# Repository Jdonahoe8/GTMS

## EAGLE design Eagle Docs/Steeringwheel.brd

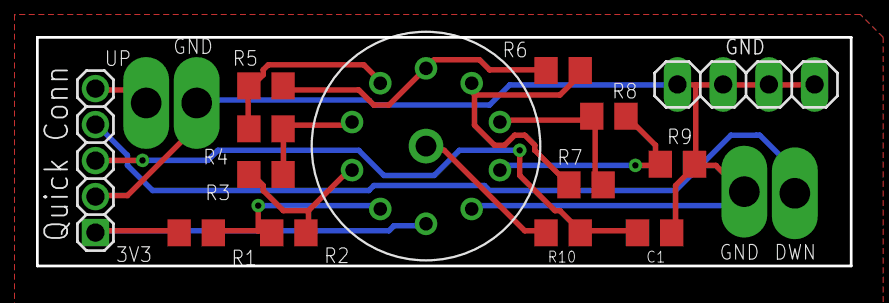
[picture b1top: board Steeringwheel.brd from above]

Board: 2 copper layers, 45.2 x 12.7 mm, 18 parts (0 on the bottom side), 14 nets.

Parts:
C1: C0805
GND: PINHD-1X4; 1X04
QUICK_CONN: PINHD-1X55X2MM; 1_05X2MM
R1, R2, R3, R4, R5, R6, R7, R8, R9, R10: R0805
SHIFT-DOWN_GND: PTR1PAD1-17Y; P1-17Y
SHIFT-DOWN_SIGNAL: PTR1PAD1-17Y; P1-17Y
SHIFT-UP_GND: PTR1PAD1-17Y; P1-17Y
SHIFT-UP_SIGNAL: PTR1PAD1-17Y; P1-17Y
U$1: 56DP36-01-1-AJN

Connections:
+5V: QUICK_CONN.1, R1.1, U$1.P1
GND: C1.1, GND.1, GND.2, GND.3, GND.4, QUICK_CONN.2, R9.2, SHIFT-DOWN_GND.TP, SHIFT-UP_GND.TP, U$1.P10
unnamed: R1.2, R2.1, U$1.P2
unnamed: R2.2, R3.1, U$1.P3
unnamed: R3.2, R4.1, U$1.P4
unnamed: R5.2, R6.1, U$1.P6
unnamed: R6.2, R7.1, U$1.P7
unnamed: R7.2, R8.1, U$1.P8
unnamed: R8.2, R9.1, U$1.P9
unnamed: QUICK_CONN.5, SHIFT-UP_SIGNAL.TP
unnamed: QUICK_CONN.4, SHIFT-DOWN_SIGNAL.TP
unnamed: R4.2, R5.1, U$1.P5
unnamed: R10.2, U$1.COMMON
OUTPUT: C1.2, QUICK_CONN.3, R10.1

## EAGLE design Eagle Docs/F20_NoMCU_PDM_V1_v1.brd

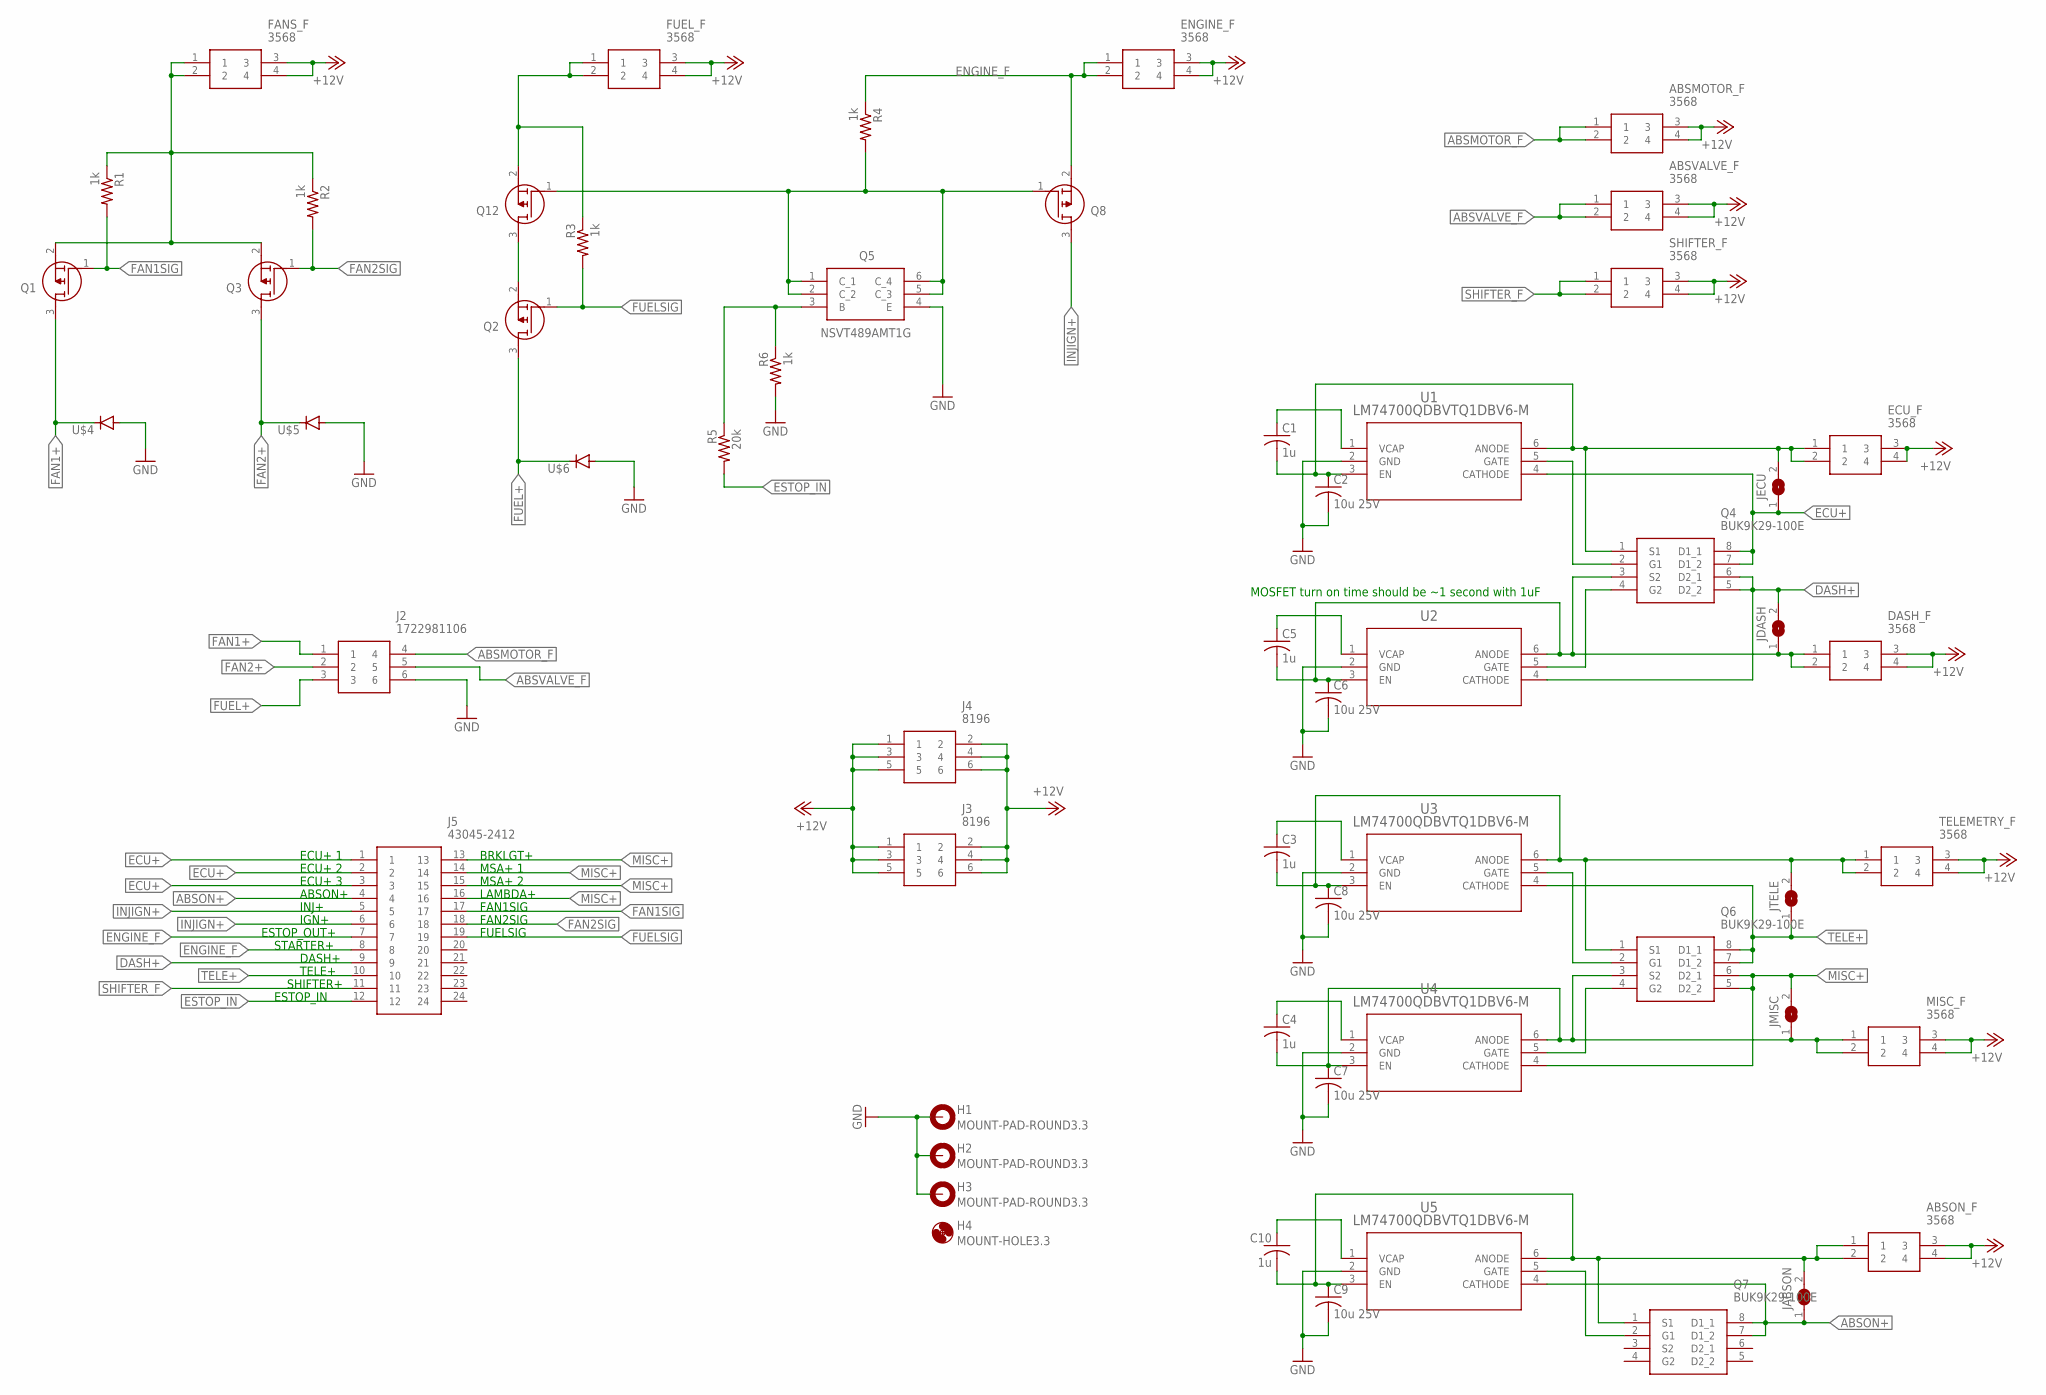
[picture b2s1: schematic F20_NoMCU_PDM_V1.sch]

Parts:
ABSMOTOR_F: 3568
ABSON_F: 3568
ABSVALVE_F: 3568
C1, C3, C4, C5, C10: 1u; C0805
C2, C6, C7, C8, C9: 10u 25V; C0805
DASH_F: 3568
ECU_F: 3568
ENGINE_F: 3568
FANS_F: 3568
FUEL_F: 3568
H1, H2, H3: MOUNT-PAD-ROUND3.3; 3,3-PAD
H4: MOUNT-HOLE3.3; 3,3
J2: 1722981106
J3, J4: 8196
J5: 43045-2412
JABSON: SJ
JDASH: SJ
JECU: SJ
JMISC: SJ
JTELE: SJ
MISC_F: 3568
Q1, Q2, Q3, Q8, Q12: IPB120P04P4L03ATMA1; PG-TO263-3-2_1
Q4, Q6, Q7: BUK9K29-100E; SOIC127P605X105-8N
Q5: NSVT489AMT1G; SOT95P275X110-6N
R1, R2, R3, R4, R6: 1k; R0805
R5: 20k; R0805
SHIFTER_F: 3568
TELEMETRY_F: 3568
U1, U2, U3, U4, U5: LM74700QDBVTQ1DBV6-M; DBV6-M
U$4, U$5, U$6: S10AL-TP; DIOM7959X265N

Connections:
+12V: ABSMOTOR_F.3, ABSMOTOR_F.4, ABSON_F.3, ABSON_F.4, ABSVALVE_F.3, ABSVALVE_F.4, DASH_F.3, DASH_F.4, ECU_F.3, ECU_F.4, ENGINE_F.3, ENGINE_F.4, FANS_F.3, FANS_F.4, FUEL_F.3, FUEL_F.4, J3.1, J3.2, J3.3, J3.4, J3.5, J3.6, J4.1, J4.2, J4.3, J4.4, J4.5, J4.6, MISC_F.3, MISC_F.4, SHIFTER_F.3, SHIFTER_F.4, TELEMETRY_F.3, TELEMETRY_F.4
ABSMOTOR_F: ABSMOTOR_F.1, ABSMOTOR_F.2, J2.4
ABSON+: J5.4, JABSON.1, Q7.7 (D1_2), Q7.8 (D1_1), U5.4 (CATHODE)
ABSVALVE_F: ABSVALVE_F.1, ABSVALVE_F.2, J2.5
DASH+: J5.9, JDASH.2, Q4.5 (D2_2), Q4.6 (D2_1), U2.4 (CATHODE)
ECU+: J5.1, J5.2, J5.3, JECU.1, Q4.7 (D1_2), Q4.8 (D1_1), U1.4 (CATHODE)
ENGINE_F: ENGINE_F.1, ENGINE_F.2, J5.7, J5.8, Q8.2 (S), R4.1
ESTOP_IN: J5.12, R5.2
FAN1+: J2.1, Q1.3 (D), U$4.C
FAN1SIG: J5.17, Q1.1 (G), R1.2
FAN2+: J2.2, Q3.3 (D), U$5.C
FAN2SIG: J5.18, Q3.1 (G), R2.2
FUEL+: J2.3, Q2.3 (D), U$6.C
FUELSIG: J5.19, Q2.1 (G), R3.2
GND: C2.2, C6.2, C7.2, C8.2, C9.2, H1.B3,3, H2.B3,3, H3.B3,3, J2.6, Q5.4 (E), R6.2, U1.2 (GND), U2.2 (GND), U3.2 (GND), U4.2 (GND), U5.2 (GND), U$4.A, U$5.A, U$6.A
INJIGN+: J5.5, J5.6, Q8.3 (D)
MISC+: J5.13, J5.14, J5.15, J5.16, JMISC.2, Q6.5 (D2_2), Q6.6 (D2_1), U4.4 (CATHODE)
unnamed: FANS_F.1, FANS_F.2, Q1.2 (S), Q3.2 (S), R1.1, R2.1
unnamed: FUEL_F.1, FUEL_F.2, Q12.2 (S), R3.1
unnamed: Q2.2 (S), Q12.3 (D)
unnamed: C1.2, C2.1, ECU_F.1, ECU_F.2, JECU.2, Q4.1 (S1), U1.3 (EN), U1.6 (ANODE)
unnamed: Q5.3 (B), R5.1, R6.1
unnamed: C1.1, U1.1 (VCAP)
unnamed: Q5.1 (C_1), Q5.2 (C_2), Q5.5 (C_3), Q5.6 (C_4), Q8.1 (G), Q12.1 (G), R4.2
unnamed: C5.1, U2.1 (VCAP)
unnamed: C5.2, C6.1, DASH_F.1, DASH_F.2, JDASH.1, Q4.3 (S2), U2.3 (EN), U2.6 (ANODE)
unnamed: ABSON_F.1, ABSON_F.2, C9.1, C10.2, JABSON.2, Q7.1 (S1), U5.3 (EN), U5.6 (ANODE)
unnamed: Q4.2 (G1), U1.5 (GATE)
unnamed: C10.1, U5.1 (VCAP)
unnamed: Q4.4 (G2), U2.5 (GATE)
unnamed: C3.1, U3.1 (VCAP)
unnamed: C4.1, U4.1 (VCAP)
unnamed: Q7.2 (G1), U5.5 (GATE)
unnamed: C4.2, C7.1, JMISC.1, MISC_F.1, MISC_F.2, Q6.3 (S2), U4.3 (EN), U4.6 (ANODE)
unnamed: C3.2, C8.1, JTELE.2, Q6.1 (S1), TELEMETRY_F.1, TELEMETRY_F.2, U3.3 (EN), U3.6 (ANODE)
unnamed: Q6.2 (G1), U3.5 (GATE)
unnamed: Q6.4 (G2), U4.5 (GATE)
SHIFTER_F: J5.11, SHIFTER_F.1, SHIFTER_F.2
TELE+: J5.10, JTELE.1, Q6.7 (D1_2), Q6.8 (D1_1), U3.4 (CATHODE)

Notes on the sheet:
ECU+ 1
ECU+ 2
ECU+ 3
ABSON+
INJ+
IGN+
ESTOP_OUT+
STARTER+
DASH+
TELE+
SHIFTER+
BRKLGT+
MSA+ 1
MSA+ 2
LAMBDA+
ESTOP_IN
MOSFET turn on time should be ~1 second with 1uF
FAN1SIG
FAN2SIG
FUELSIG

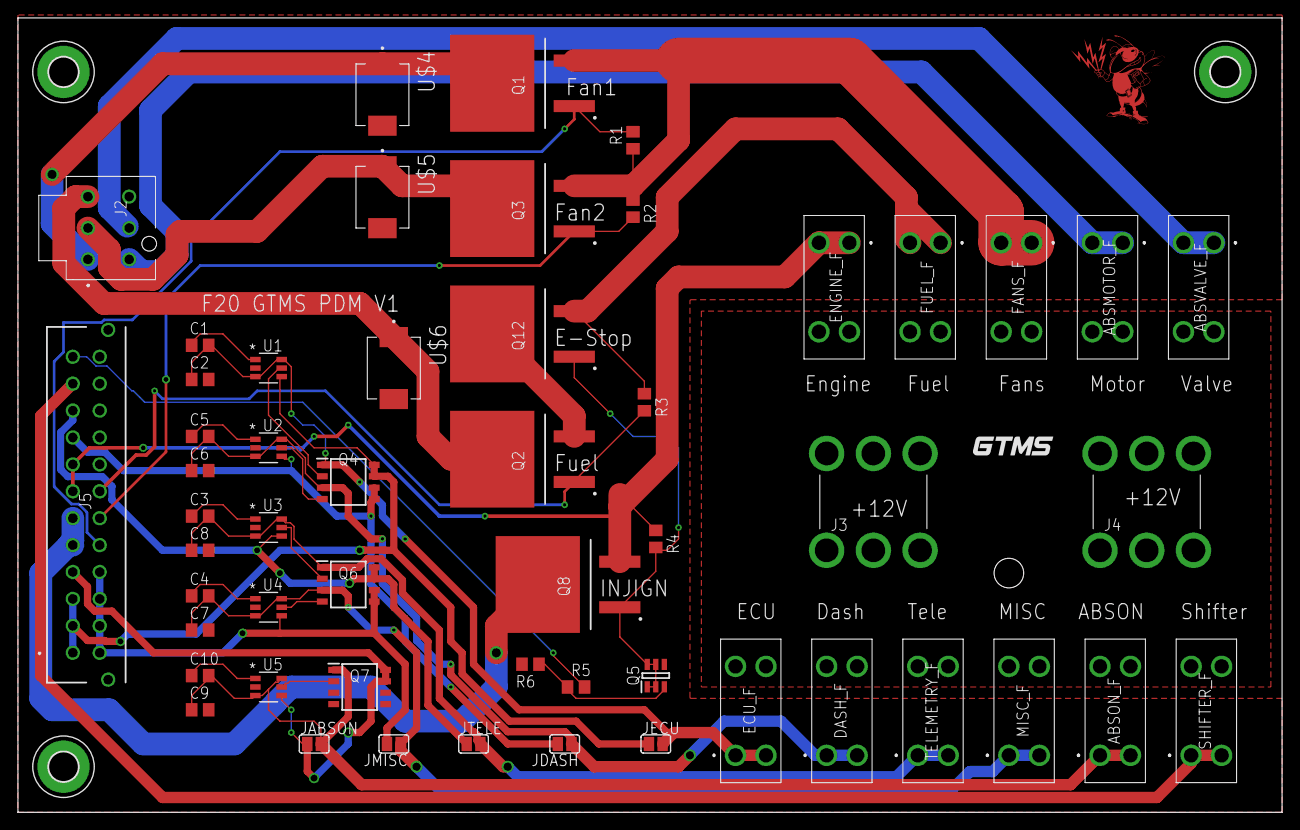
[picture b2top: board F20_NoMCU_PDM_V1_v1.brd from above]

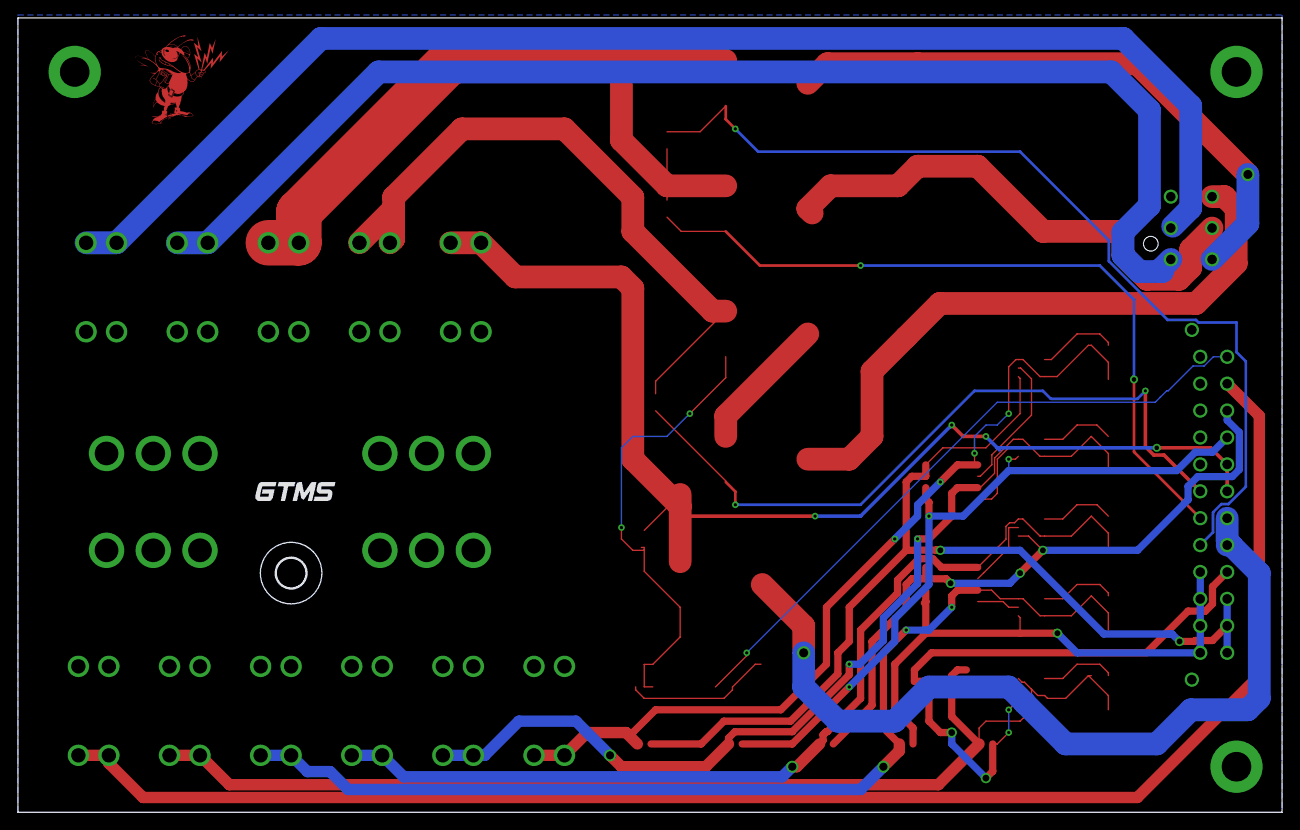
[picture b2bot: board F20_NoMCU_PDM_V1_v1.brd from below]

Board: 2 copper layers, 140.9 x 88.6 mm, 60 parts (2 on the bottom side), 39 nets.

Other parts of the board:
U$1, U$3: GTMS
U$2: ECE_BUZZ

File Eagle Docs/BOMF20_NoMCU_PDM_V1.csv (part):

"Part";"Value";"Device";"Package";"Description";"COPYRIGHT";"DESCRIPTION";"HEIGHT";"MANUFACTURER_NAME";"MANUFACTURER_PART_NUMBER";"MOUSER2_PART_NUMBER";"MOUSER2_PRICE-STOCK";"MOUSER_PART_NUMBER";"MOUSER_PRICE-STOCK";"POPULARITY";"SPICEPREFIX";"VENDOR";
"ABSMOTOR_F";"3568";"3568";"3568";"Fuse Holder .63 MINI FUSE HOLDER";"";"Fuse Holder .63 MINI FUSE HOLDER";"7.37mm";"Keystone Electronics";"3568";"";"";"534-3568";"https://www.mouser.com/Search/Refine.aspx?Keyword=534-3568";"";"";"";
"ABSON_F";"3568";"3568";"3568";"Fuse Holder .63 MINI FUSE HOLDER";"";"Fuse Holder .63 MINI FUSE HOLDER";"7.37mm";"Keystone Electronics";"3568";"";"";"534-3568";"https://www.mouser.com/Search/Refine.aspx?Keyword=534-3568";"";"";"";
"ABSVALVE_F";"3568";"3568";"3568";"Fuse Holder .63 MINI FUSE HOLDER";"";"Fuse Holder .63 MINI FUSE HOLDER";"7.37mm";"Keystone Electronics";"3568";"";"";"534-3568";"https://www.mouser.com/Search/Refine.aspx?Keyword=534-3568";"";"";"";
"C1";"1u";"C-USC0805";"C0805";"CAPACITOR, American symbol";"";"";"";"";"";"";"";"";"";"63";"C";"";
"C2";"10u 25V";"C-USC0805";"C0805";"CAPACITOR, American symbol";"";"";"";"";"";"";"";"";"";"63";"C";"";
"C3";"1u";"C-USC0805";"C0805";"CAPACITOR, American symbol";"";"";"";"";"";"";"";"";"";"63";"C";"";
"C4";"1u";"C-USC0805";"C0805";"CAPACITOR, American symbol";"";"";"";"";"";"";"";"";"";"63";"C";"";
"C5";"1u";"C-USC0805";"C0805";"CAPACITOR, American symbol";"";"";"";"";"";"";"";"";"";"63";"C";"";
"C6";"10u 25V";"C-USC0805";"C0805";"CAPACITOR, American symbol";"";"";"";"";"";"";"";"";"";"63";"C";"";
"C7";"10u 25V";"C-USC0805";"C0805";"CAPACITOR, American symbol";"";"";"";"";"";"";"";"";"";"63";"C";"";
"C8";"10u 25V";"C-USC0805";"C0805";"CAPACITOR, American symbol";"";"";"";"";"";"";"";"";"";"63";"C";"";
"C9";"10u 25V";"C-USC0805";"C0805";"CAPACITOR, American symbol";"";"";"";"";"";"";"";"";"";"63";"C";"";
"C10";"1u";"C-USC0805";"C0805";"CAPACITOR, American symbol";"";"";"";"";"";"";"";"";"";"63";"C";"";
"DASH_F";"3568";"3568";"3568";"Fuse Holder .63 MINI FUSE HOLDER";"";"Fuse Holder .63 MINI FUSE HOLDER";"7.37mm";"Keystone Electronics";"3568";"";"";"534-3568";"https://www.mouser.com/Search/Refine.aspx?Keyword=534-3568";"";"";"";
"ECU_F";"3568";"3568";"3568";"Fuse Holder .63 MINI FUSE HOLDER";"";"Fuse Holder .63 MINI FUSE HOLDER";"7.37mm";"Keystone Electronics";"3568";"";"";"534-3568";"https://www.mouser.com/Search/Refine.aspx?Keyword=534-3568";"";"";"";
"ENGINE_F";"3568";"3568";"3568";"Fuse Holder .63 MINI FUSE HOLDER";"";"Fuse Holder .63 MINI FUSE HOLDER";"7.37mm";"Keystone Electronics";"3568";"";"";"534-3568";"https://www.mouser.com/Search/Refine.aspx?Keyword=534-3568";"";"";"";
"FANS_F";"3568";"3568";"3568";"Fuse Holder .63 MINI FUSE HOLDER";"";"Fuse Holder .63 MINI FUSE HOLDER";"7.37mm";"Keystone Electronics";"3568";"";"";"534-3568";"https://www.mouser.com/Search/Refine.aspx?Keyword=534-3568";"";"";"";
"FUEL_F";"3568";"3568";"3568";"Fuse Holder .63 MINI FUSE HOLDER";"";"Fuse Holder .63 MINI FUSE HOLDER";"7.37mm";"Keystone Electronics";"3568";"";"";"534-3568";"https://www.mouser.com/Search/Refine.aspx?Keyword=534-3568";"";"";"";
"H1";"MOUNT-PAD-ROUND3.3";"MOUNT-PAD-ROUND3.3";"3,3-PAD";"MOUNTING PAD, round";"";"";"";"";"";"";"";"";"";"1";"";"";
"H2";"MOUNT-PAD-ROUND3.3";"MOUNT-PAD-ROUND3.3";"3,3-PAD";"MOUNTING PAD, round";"";"";"";"";"";"";"";"";"";"1";"";"";
"H3";"MOUNT-PAD-ROUND3.3";"MOUNT-PAD-ROUND3.3";"3,3-PAD";"MOUNTING PAD, round";"";"";"";"";"";"";"";"";"";"1";"";"";
"H4";"MOUNT-HOLE3.3";"MOUNT-HOLE3.3";"3,3";"MOUNTING HOLE with drill center marker";"";"";"";"";"";"";"";"";"";"3";"";"";
"J2";"1722981106";"1722981106";"1722981106";"ULTRAFIT CONN HDR 06CKT";"";"ULTRAFIT CONN HDR 06CKT";"14mm";"Molex";"1722981106";"";"";"";"";"";"";"";
"J3";"8196";"8196";"8196";"Terminal; 10-32; Stainless Steel; 3/8 in.; 0.679 in.; 0.679 in.; Brass; Tin";"";"Terminal";" 10-32";" Stainless Steel";" 3/8 in.";" 0.679 in.";" 0.679 in.";" Brass";" Tin";"11.51mm";"Keystone Electronics";"8196";
"J4";"8196";"8196";"8196";"Terminal; 10-32; Stainless Steel; 3/8 in.; 0.679 in.; 0.679 in.; Brass; Tin";"";"Terminal";" 10-32";" Stainless Steel";" 3/8 in.";" 0.679 in.";" 0.679 in.";" Brass";" Tin";"11.51mm";"Keystone Electronics";"8196";
"J5";"43045-2412";"43045-2412";"43045-2412";"Header 3.00mm, WTB, dual row, vert,24w Molex MICRO-FIT 3.0 Series, Series Number 43045, 3mm Pitch 24 Way 2 Row Shrouded Straight PCB Header, Through Hole";"";"Header 3.00mm, WTB, dual row, vert,24w Molex MICRO-FIT 3.0 Series, Series Number 43045, 3mm Pitch 24 Way 2 Row Shrouded Straight PCB Header, Through Hole";"mm";"Molex";"43045-2412";"";"";"538-43045-2412";"https://www.mouser.com/Search/Refine.aspx?Keyword=538-43045-2412";"";"";"";
"JABSON";"";"SJ";"SJ";"SMD solder JUMPER";"";"";"";"";"";"";"";"";"";"33";"";"";
"JDASH";"";"SJ";"SJ";"SMD solder JUMPER";"";"";"";"";"";"";"";"";"";"33";"";"";
"JECU";"";"SJ";"SJ";"SMD solder JUMPER";"";"";"";"";"";"";"";"";"";"33";"";"";
"JMISC";"";"SJ";"SJ";"SMD solder JUMPER";"";"";"";"";"";"";"";"";"";"33";"";"";
"JTELE";"";"SJ";"SJ";"SMD solder JUMPER";"";"";"";"";"";"";"";"";"";"33";"";"";
"MISC_F";"3568";"3568";"3568";"Fuse Holder .63 MINI FUSE HOLDER";"";"Fuse Holder .63 MINI FUSE HOLDER";"7.37mm";"Keystone Electronics";"3568";"";"";"534-3568";"https://www.mouser.com/Search/Refine.aspx?Keyword=534-3568";"";"";"";
"Q1";"IPB120P04P4L03ATMA1";"IPB120P04P4L03ATMA1";"PG-TO263-3-2_1";"IPB120P04P4L03ATMA1 P-Channel MOSFET, 120 A, 40 V OptiMOS P, 3-Pin D2PAK Infineon";"";"IPB120P04P4L03ATMA1 P-Channel MOSFET, 120 A, 40 V OptiMOS P, 3-Pin D2PAK Infineon";"mm";"Infineon";"IPB120P04P4L03ATMA1";"";"";"726-IPB120P04P4L03AT";"https://www.mouser.com/Search/Refine.aspx?Keyword=726-IPB120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";"";"";"";
"Q2";"IPB120P04P4L03ATMA1";"IPB120P04P4L03ATMA1";"PG-TO263-3-2_1";"IPB120P04P4L03ATMA1 P-Channel MOSFET, 120 A, 40 V OptiMOS P, 3-Pin D2PAK Infineon";"";"IPB120P04P4L03ATMA1 P-Channel MOSFET, 120 A, 40 V OptiMOS P, 3-Pin D2PAK Infineon";"mm";"Infineon";"IPB120P04P4L03ATMA1";"";"";"726-IPB120P04P4L03AT";"https://www.mouser.com/Search/Refine.aspx?Keyword=726-IPB120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";"";"";"";
"Q3";"IPB120P04P4L03ATMA1";"IPB120P04P4L03ATMA1";"PG-TO263-3-2_1";"IPB120P04P4L03ATMA1 P-Channel MOSFET, 120 A, 40 V OptiMOS P, 3-Pin D2PAK Infineon";"";"IPB120P04P4L03ATMA1 P-Channel MOSFET, 120 A, 40 V OptiMOS P, 3-Pin D2PAK Infineon";"mm";"Infineon";"IPB120P04P4L03ATMA1";"";"";"726-IPB120P04P4L03AT";"https://www.mouser.com/Search/Refine.aspx?Keyword=726-IPB120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";"";"";"";
"Q4";"BUK9K29-100E";"BUK9K29-100E";"SOIC127P605X105-8N";"NPN/PNP high power double bipolar transistor in a SOT1205 (LFPAK56D) Surface Mounted Device (SMD) power plastic package";"";"NPN/PNP high power double bipolar transistor in a SOT1205 (LFPAK56D) Surface Mounted Device (SMD) power plastic package";"1.05mm";"Nexperia";"PHPT610030NPKX";"771-PHPT610030NPKX";"https://www.mouser.com/Search/Refine.aspx?Keyword=771-PHPT61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";"";"";"";"";"";
"Q5";"NSVT489AMT1G";"NSVT489AMT1G";"SOT95P275X110-6N";"NPN Bipolar Transistor, 2 A 30 V, 6-pin TSOP";"";"NPN Bipolar Transistor, 2 A 30 V, 6-pin TSOP";"1.1mm";"ON Semiconductor";"NSVT489AMT1G";"";"";"863-NSVT489AMT1G";"https://www.mouser.com/Search/Refine.aspx?Keyword=863-NSVT489AMT1G";"";"";"";
"Q6";"BUK9K29-100E";"BUK9K29-100E";"SOIC127P605X105-8N";"NPN/PNP high power double bipolar transistor in a SOT1205 (LFPAK56D) Surface Mounted Device (SMD) power plastic package";"";"NPN/PNP high power double bipolar transistor in a SOT1205 (LFPAK56D) Surface Mounted Device (SMD) power plastic package";"1.05mm";"Nexperia";"PHPT610030NPKX";"771-PHPT610030NPKX";"https://www.mouser.com/Search/Refine.aspx?Keyword=771-PHPT61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";"";"";"";"";"";
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
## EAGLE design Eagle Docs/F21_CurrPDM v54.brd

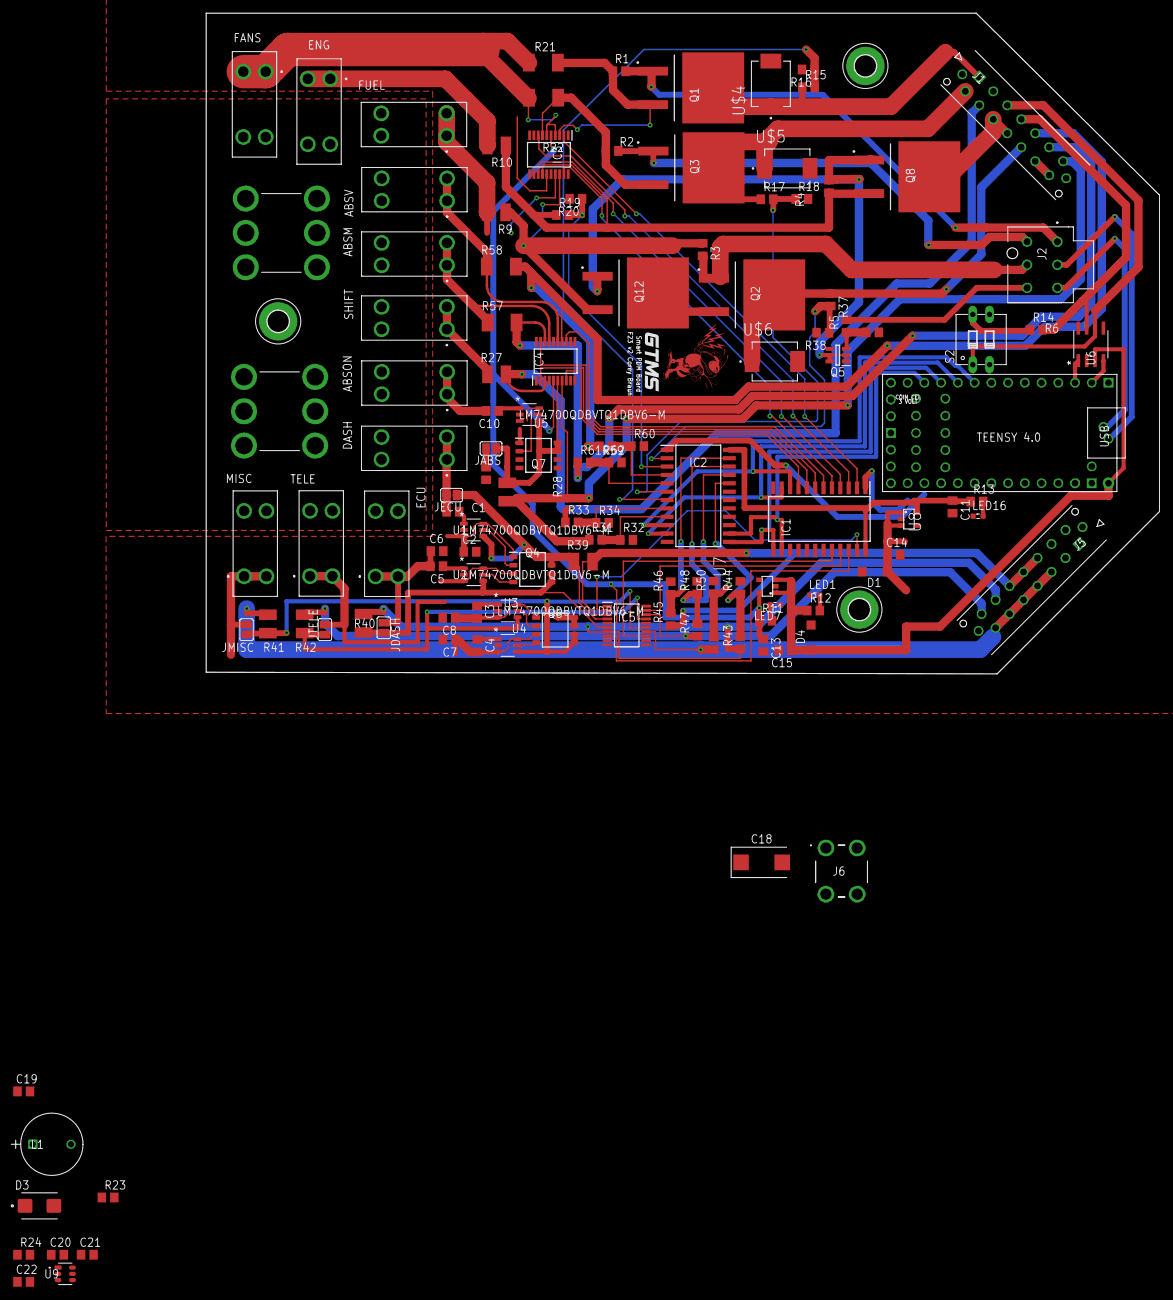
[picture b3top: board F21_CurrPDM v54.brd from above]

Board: 2 copper layers, 144.7 x 100.3 mm, 129 parts (0 on the bottom side), 97 nets.

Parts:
ABSM: 3568
ABSON: 3568
ABSV: 3568
C1, C3, C4, C5, C10: 1u; C0805
C2, C6, C7, C8: 10u 25V; C0805
C9: .1uF 12V; C0805
C11, C13, C14, C15, C20, C21, C22: C0805
C18: CAPMP7343X310N
C19: .1uF; C0805
D1, D4: SOD123
D3: MURS110T3G; DIOM5436X247N
DASH: 3568
ECU: 3568
ENG: 3568
FANS: 3568
FUEL: 3568
H1, H2, H3: MOUNT-PAD-ROUND3.3; 3,3-PAD
IC1, IC2: CD74HC4067M96; SOIC127P1030X265-24N
IC3, IC4, IC5: INA4181A2IPWR; SOP65P640X120-20N
J1, J5: 43045-1424; 43045-14YY_24,25,26
J2: 1722981106
J3, J4: 8196
J6: 8195
JABS: SJ
JDASH: SJ
JECU: SJ
JMISC: SJ
JTELE: SJ
L1: RLB0914-4R7ML; IND_BOURNS_RLB0914
LED1, LED7, LED16: SML0603
MISC: 3568
Q1, Q2, Q3, Q8, Q12: IPB120P04P4L03ATMA1; PG-TO263-3-2_1
Q4, Q6, Q7: BUK9K29-100E; SOIC127P605X105-8N
Q5: NSVT489AMT1G; SOT95P275X110-6N
R1, R2, R3, R4, R6: 1k; R0805
R5: 20k; R0805
R9, R10, R27, R28, R39, R40, R41, R42: 0.02; R1210
R11, R12, R13: 330; R0805
R14, R23, R24: R0805
R15, R17, R19, R31, R33, R37, R43, R45, R47, R49, R59, R61: 36k; R0805
R16, R18, R20, R32, R34, R38, R44, R46, R48, R50, R60, R62: 10k; R0805
R21, R22, R57, R58: 0.005; R2010
S2: DIP02YL
SHIFT: 3568
TELE: 3568
U1, U2, U3, U4, U5: LM74700QDBVTQ1DBV6-M; DBV6-M
U6: NCV7349D10R2G; SOIC8
U7, U8: NCP114AMX330T1GTSOP-5; TSOP-5
U9: AP3211KTR-G1; SOT23-6
U$1: TEENSY40
U$2: ECE_BUZZ
U$3: GTMS
U$4, U$5, U$6: S10AL-TP; DIOM7959X265N

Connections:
+3V3_A1: C13.1, IC3.5, IC4.5, R11.1, U7.5
+3V3_A2: C11.1, C18.1, IC1.24, IC2.24, R13.1, U8.5
+5V: C14.1, C15.1, C21.1, D1.C, D4.C, J6.1, J6.2, J6.3, J6.4, L1.1, R12.1, R23.2, U6.3, U7.1, U7.3, U8.1, U8.3, U$1.VIN
+12V: ABSM.3, ABSM.4, ABSON.3, ABSON.4, ABSV.3, ABSV.4, DASH.3, DASH.4, ECU.3, ECU.4, ENG.3, ENG.4, FANS.3, FANS.4, FUEL.3, FUEL.4, J3.1, J3.2, J3.3, J3.4, J3.5, J3.6, J4.1, J4.2, J4.3, J4.4, J4.5, J4.6, MISC.3, MISC.4, SHIFT.3, SHIFT.4, TELE.3, TELE.4
ABSMOTOR_F: ABSM.1, ABSM.2, IC4.17, R57.1
ABSMOTOR_I: IC1.7, IC4.19
ABSMOTOR_OUT: IC4.18, J1.6, R57.2, R61.1
ABSON+: C19.1, IC4.6, JABS.1, Q7.7, Q7.8, R28.1, U5.4
ABSON_I: IC1.9, IC4.8
ABSON_OUT: IC4.7, J1.7, R28.2, R31.1
ABSVALVE_F: ABSV.1, ABSV.2, IC4.15, R58.1
ABSVALVE_I: IC1.6, IC4.13
ABSVALVE_OUT: IC4.14, J1.5, R58.2, R59.1
CAN_H: J1.4, R14.2, U6.7
CAN_L: J1.3, S2.1, U6.6
CAN_RX: U6.4, U$1.0-RX1
CAN_TX: U6.1, U$1.1-TX1
DASH+: IC5.6, JDASH.2, Q4.5, Q4.6, R40.1, U2.4
DASH_I: IC1.22, IC5.8
DASH_OUT: IC5.7, J5.13, R40.2, R43.1
ECU+: IC5.4, JECU.1, Q4.7, Q4.8, R39.1, U1.4
ECU_I: IC1.23, IC5.2
ECU_OUT: IC5.3, J5.10, J5.11, J5.12, R39.2, R45.1
ENGINE+: IC3.14, Q8.2, R4.1, R10.1, R19.1
ENGINE_F: ENG.1, ENG.2, IC3.15, R10.2
ENGINE_I: IC1.4, IC3.13
ENGINE_OUT: J1.13, J1.14
ESTOP_IN: J2.6, R5.2
FAN1+: IC3.3, Q1.2, R1.1, R21.1
FAN1SIG: J2.1, Q1.1, R1.2
FAN1_I: IC1.2, IC3.2
FAN1_OUT: J1.1, Q1.3, R15.1, U$4.C
FAN2+: IC3.7, Q3.2, R2.1, R22.1
FAN2SIG: J2.4, Q3.1, R2.2
FAN2_I: IC1.3, IC3.8
FAN2_OUT: J1.8, Q3.3, R17.1, U$5.C
FANS_F: FANS.1, FANS.2, IC3.4, IC3.6, R21.2, R22.2
FUEL+: IC3.18, Q12.2, R3.1, R9.1
FUELSIG: J2.5, Q2.1, R3.2
FUEL_F: FUEL.1, FUEL.2, IC3.17, R9.2
FUEL_I: IC1.5, IC3.19
FUEL_OUT: J1.12, Q2.3, R37.1, U$6.C
GND: C2.2, C6.2, C7.2, C8.2, C9.2, C11.2, C13.2, C14.2, C15.2, C19.2, C21.2, C22.2, D1.A, D3.A, D4.A, H1.B3,3, H2.B3,3, H3.B3,3, IC1.12, IC1.15, IC2.12, IC2.15, IC3.1, IC3.9, IC3.12, IC3.16, IC3.20, IC4.1, IC4.9, IC4.12, IC4.16, IC4.20, IC5.1, IC5.9, IC5.12, IC5.16, IC5.20, J1.15, J1.16, J5.15, J5.16, LED1.C, LED7.C, LED16.C, Q5.4, R6.2, R16.2, R18.2, R20.2, R24.1, R32.2, R34.2, R38.2, R44.2, R46.2, R48.2, R50.2, R60.2, R62.2, U1.2, U2.2, U3.2, U4.2, U5.2, U6.2, U6.8, U7.2, U8.2, U9.2, U$1.GND1, U$1.GND2, U$1.GND3, U$4.A, U$5.A, U$6.A
INJIGN_OUT: J1.10, J1.11, Q8.3
MICS_OUT: IC5.14, J5.3, J5.4, J5.5, J5.6, J5.7, R41.1, R49.1
MISC+: IC5.15, JMISC.2, Q6.5, Q6.6, R41.2, U4.4
MISC_I: IC1.20, IC5.13
unnamed: C1.2, C2.1, ECU.1, ECU.2, JECU.2, Q4.1, U1.3, U1.6
unnamed: C20.1, U9.1
unnamed: Q2.2, Q12.3
unnamed: LED16.A, R13.2
unnamed: Q5.3, R5.1, R6.1
unnamed: C1.1, U1.1
unnamed: Q5.1, Q5.2, Q5.5, Q5.6, Q8.1, Q12.1, R4.2
unnamed: C5.1, U2.1
unnamed: C20.2, D3.C, L1.2, U9.6
unnamed: R23.1, R24.2, U9.3
unnamed: Q4.2, U1.5
unnamed: C22.1, U9.4, U9.5
unnamed: C10.1, U5.1
unnamed: Q4.4, U2.5
unnamed: C3.1, U3.1
unnamed: C4.1, U4.1
unnamed: Q7.2, U5.5
unnamed: LED1.A, R12.2
unnamed: Q6.2, U3.5
unnamed: Q6.4, U4.5
unnamed: LED7.A, R11.2
unnamed: R14.1, S2.4
SHIFTER_F: IC4.4, R27.1, SHIFT.1, SHIFT.2
SHIFTER_F1: C5.2, C6.1, DASH.1, DASH.2, JDASH.1, Q4.3, U2.3, U2.6
SHIFTER_F2: C3.2, C8.1, JTELE.2, Q6.1, TELE.1, TELE.2, U3.3, U3.6
SHIFTER_F3: C4.2, C7.1, JMISC.1, MISC.1, MISC.2, Q6.3, U4.3, U4.6
SHIFTER_F4: ABSON.1, ABSON.2, C9.1, C10.2, JABS.2, Q7.1, U5.3, U5.6
SHIFTER_I: IC1.8, IC4.2
SHIFTER_OUT: IC4.3, J1.9, R27.2, R33.1
S_0: IC1.10, IC2.10, U$1.7-RX2/OUT1A
S_1: IC1.11, IC2.11, U$1.8-TX2/IN1
S_2: IC1.14, IC2.14, U$1.10-CS/MQSR
S_3: IC1.13, IC2.13, U$1.9-OUT1C
TELE+: IC5.17, JTELE.1, Q6.7, Q6.8, R42.2, U3.4
TELE_I: IC1.21, IC5.19
TELE_OUT: IC5.18, J5.14, R42.1, R47.1
USB+: J2.3, U$1.D+
USB-: J2.2, U$1.D-
V_ABSMOTOR: IC2.5, R61.2, R62.1
V_ABSON: IC2.9, R31.2, R32.1
V_ABSVALVE: IC2.4, R59.2, R60.1
V_DASH: IC2.20, R43.2, R44.1
V_ECU: IC2.23, R45.2, R46.1
V_ENGINE: IC2.3, R19.2, R20.1
V_FAN1: IC2.7, R15.2, R16.1
V_FAN2: IC2.6, R17.2, R18.1
V_FUEL: IC2.2, R37.2, R38.1
V_MISC: IC2.21, R49.2, R50.1
V_SHIFTER: IC2.8, R33.2, R34.1
V_TELE: IC2.22, R47.2, R48.1

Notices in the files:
Eagle Docs/BOMF20_NoMCU_PDM_V1.csv:
"LM74700QDBVTQ1DBV6-M";"LM74700QDBVTQ1DBV6-M";"DBV6-M";"";"Copyright (C) 2016 Accelerated Designs. All rights reserved";"";"";"";"LM74700QDBVTQ1";"";"";"";"";"";"";"Texas Instruments";
parts and their libraries:
LM74700: COPYRIGHT: Copyright (C) 2016 Accelerated Designs. All rights reserved
